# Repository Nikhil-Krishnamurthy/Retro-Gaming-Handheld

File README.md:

# Retro-Gaming-Handheld
This project was creating a gaming handheld from scratch, including cadding the case and designing the pcb. This handheld will run retro games up to the SNES.

Key Features
Esp32 powered emulation   
RGB444 7in screen    
Dedicated sound system    
Cold swappable storage system    
Rechargable 3500mAh battery    
USB C data transfer to computer    
USB C powered charging    

Schematic   

Power   

Buttons   

Screen   

Data   

Sound   

ESP 32   

PCB Layout   

Case

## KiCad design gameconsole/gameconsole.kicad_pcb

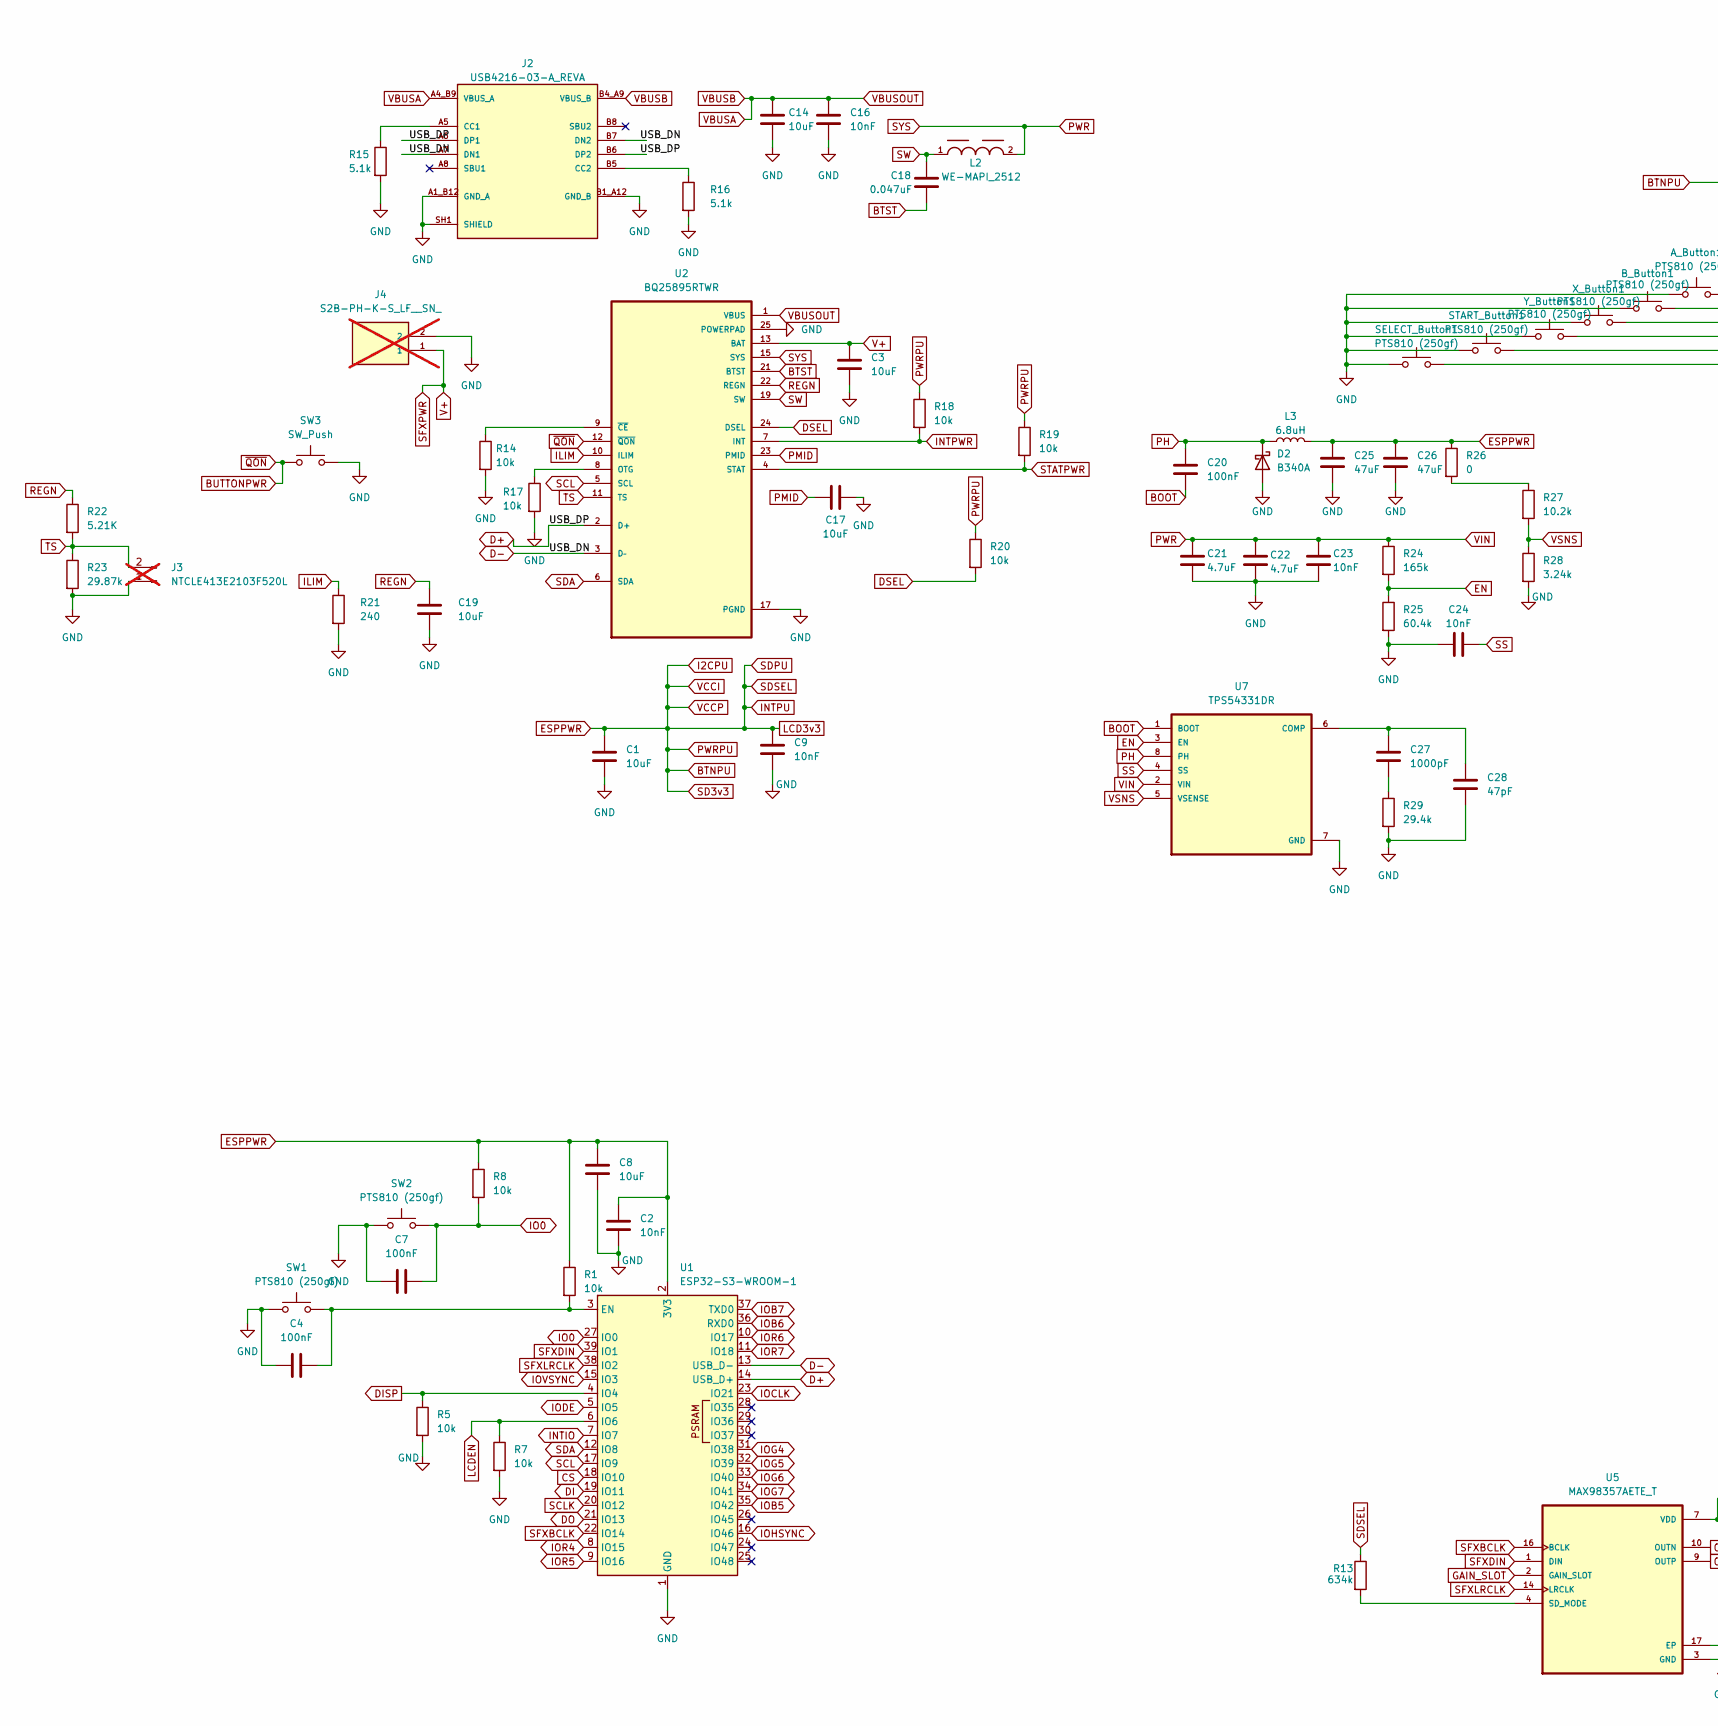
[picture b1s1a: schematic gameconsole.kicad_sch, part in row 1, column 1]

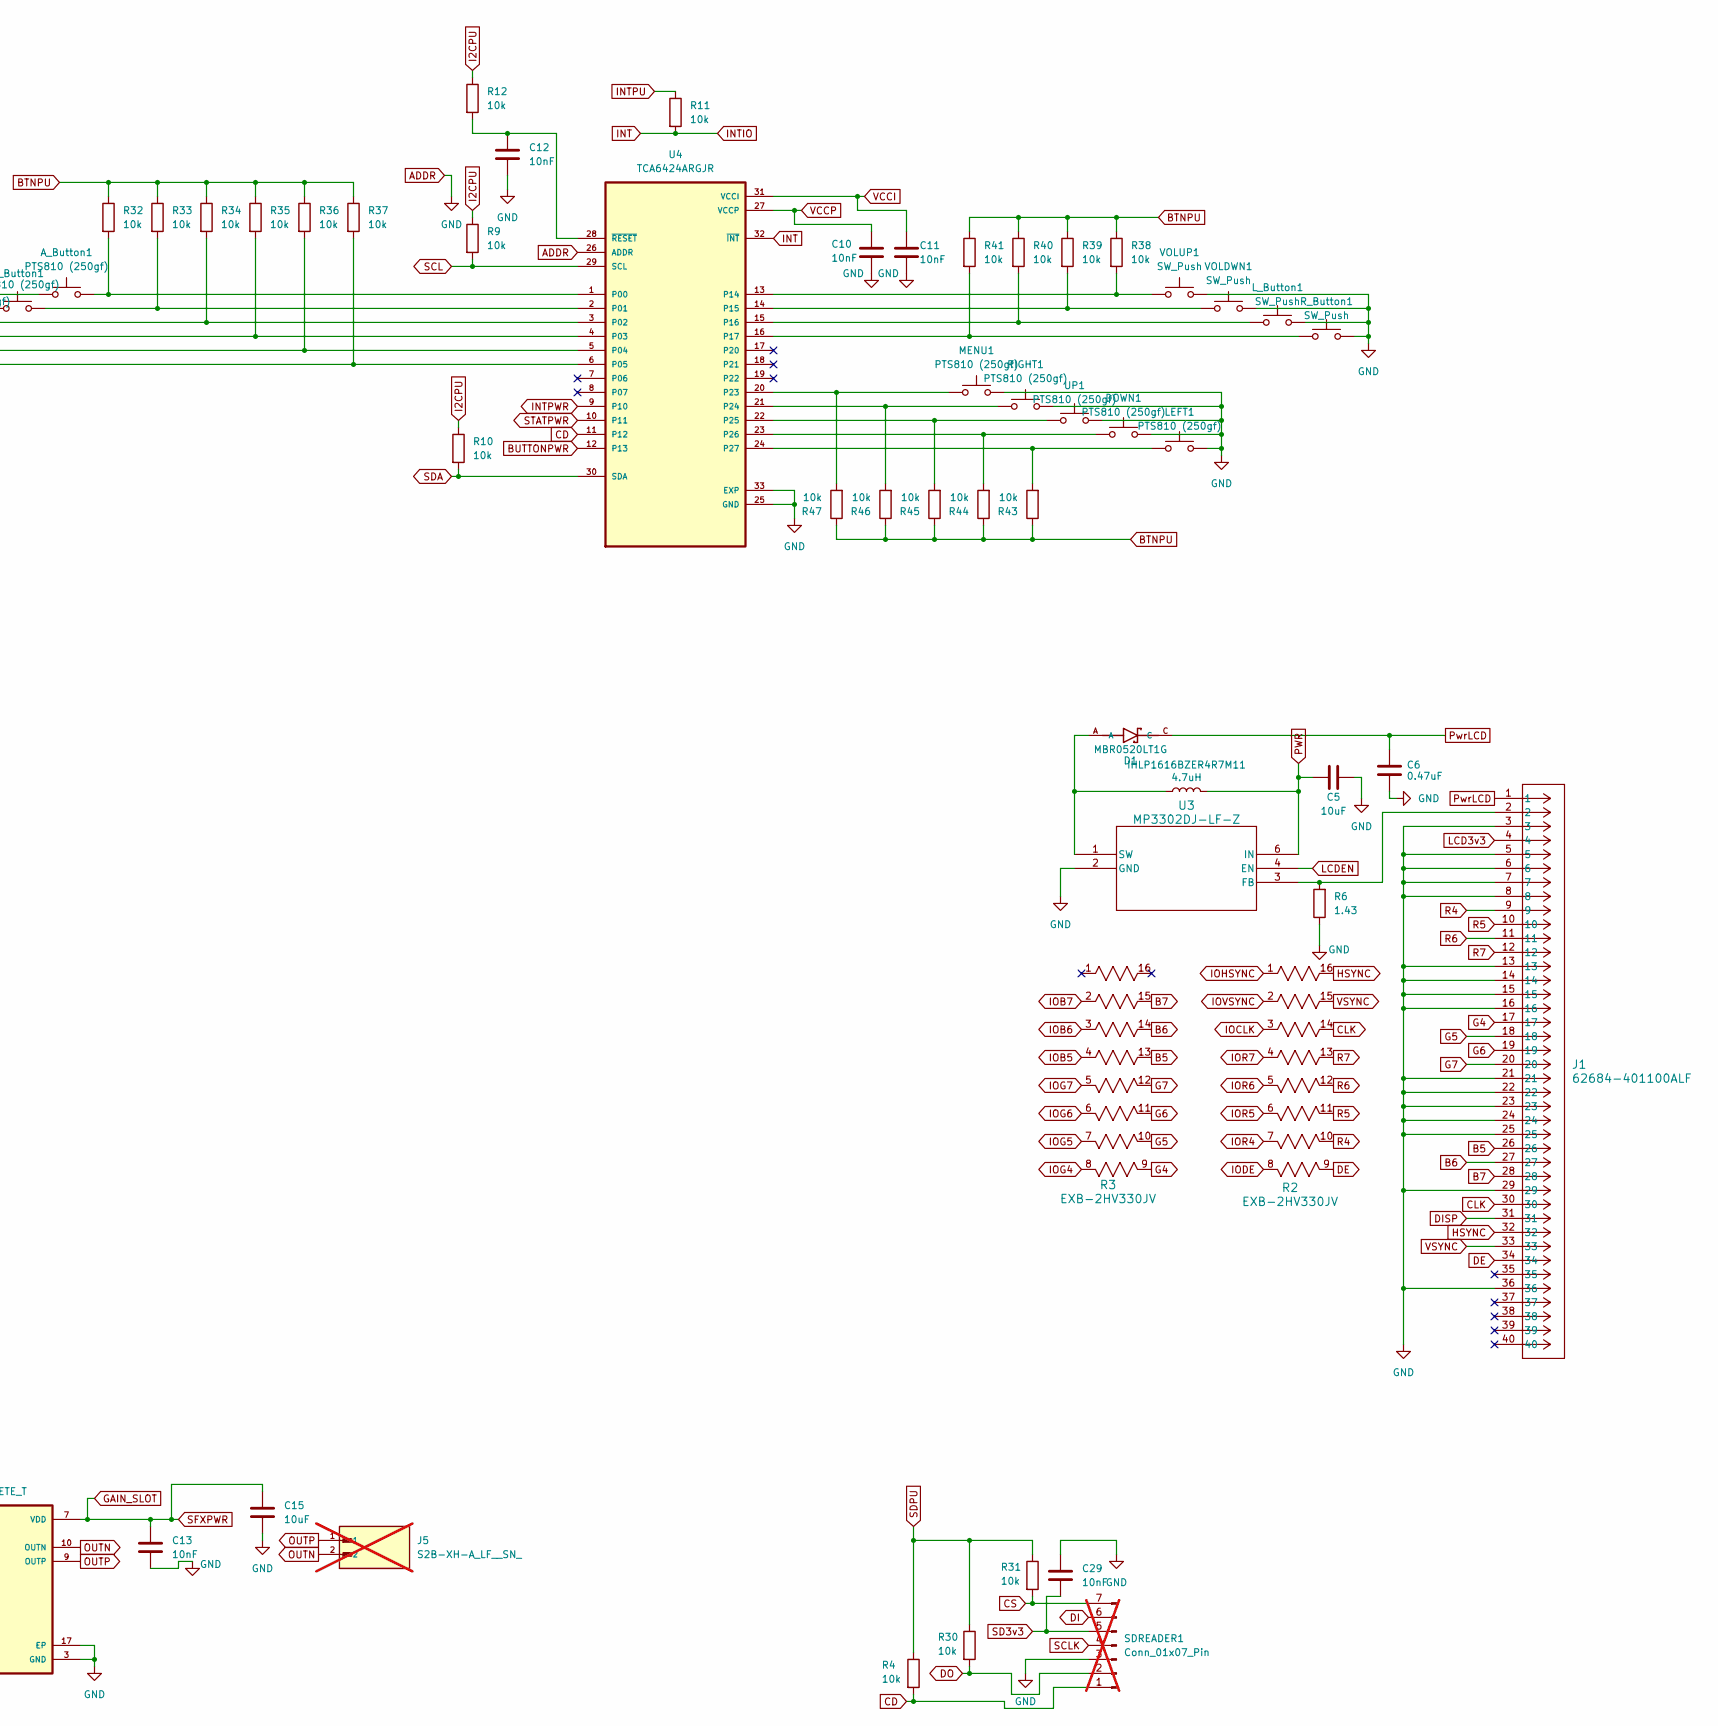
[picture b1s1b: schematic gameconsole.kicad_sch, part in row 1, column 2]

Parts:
A_Button1: PTS810 (250gf); SW_PTS810_SJM_250_SMTR_LFS
B_Button1: PTS810 (250gf); SW_PTS810_SJM_250_SMTR_LFS
C1, C3, C5, C8, C14, C15, C17, C19: 10uF; CAPC3216X180N
C2, C9, C10, C11, C12, C13, C16, C23, C24, C29: 10nF; CAPC1608X90N
C4, C7, C20: 100nF; CAPC1608X90N
C6: 0.47uF; CAPC1608X90N
C18: 0.047uF; C_0805_2012Metric_Pad1.18x1.45mm_HandSolder
C21, C22: 4.7uF; CAPC3216X180N
C25, C26: 47uF; CAPC3216X180N
C27: 1000pF; C_0805_2012Metric_Pad1.18x1.45mm_HandSolder
C28: 47pF; C_0805_2012Metric_Pad1.18x1.45mm_HandSolder
D1: MBR0520LT1G; SOD3716X135N
D2: B340A; DIOM5226X230N
DOWN1: PTS810 (250gf); SW_PTS810_SJM_250_SMTR_LFS
IHLP1616BZER4R7M11: 4.7uH; IND_IHLP-1616BZ_VIS
J1: 62684-401100ALF; CONN_62684-401100ALF_AMP
J2: USB4216-03-A_REVA; GCT_USB4216-03-A_REVA; PARTREV A
J3: NTCLE413E2103F520L; JST_S2B-PH-K-S_LF__SN_; not fitted
J4: S2B-PH-K-S_LF__SN_; JST_S2B-PH-K-S_LF__SN_; not fitted
J5: S2B-XH-A_LF__SN_; JST_S2B-XH-A_LF__SN_; PARTREV 27-1-20; not fitted
L2: WE-MAPI_2512; WE-MAPI_4020
L3: 6.8uH; INDPM7366X300N
LEFT1: PTS810 (250gf); SW_PTS810_SJM_250_SMTR_LFS
L_Button1: SW_Push; SW_TL3330AF130QG
MENU1: PTS810 (250gf); SW_PTS810_SJM_250_SMTR_LFS
R1, R4, R5, R7, R8, R9, R10, R11, R12, R14, R17, R18, R19, R20, R30, R31, R32, R33, R34, R35, R36, R37, R38, R39, R40, R41, R43, R44, R45, R46, R47: 10k; R_0805_2012Metric_Pad1.20x1.40mm_HandSolder
R2, R3: EXB-2HV330JV; RESCAXE50P380X160X55-16N
R6: 1.43; R_0805_2012Metric_Pad1.20x1.40mm_HandSolder
R13: 634k; R_0805_2012Metric_Pad1.20x1.40mm_HandSolder
R15, R16: 5.1k; R_0805_2012Metric_Pad1.20x1.40mm_HandSolder
R21: 240; R_0805_2012Metric_Pad1.20x1.40mm_HandSolder
R22: 5.21K; R_0805_2012Metric_Pad1.20x1.40mm_HandSolder
R23: 29.87k; R_0805_2012Metric_Pad1.20x1.40mm_HandSolder
R24: 165k; R_0805_2012Metric_Pad1.20x1.40mm_HandSolder
R25: 60.4k; R_0805_2012Metric_Pad1.20x1.40mm_HandSolder
R26: 0; R_0805_2012Metric_Pad1.20x1.40mm_HandSolder
R27: 10.2k; R_0805_2012Metric_Pad1.20x1.40mm_HandSolder
R28: 3.24k; R_0805_2012Metric_Pad1.20x1.40mm_HandSolder
R29: 29.4k; R_0805_2012Metric_Pad1.20x1.40mm_HandSolder
RIGHT1: PTS810 (250gf); SW_PTS810_SJM_250_SMTR_LFS
R_Button1: SW_Push; SW_TL3330AF130QG
SDREADER1: Conn_01x07_Pin; PinHeader_1x07_P2.54mm_Vertical; not fitted
SELECT_Button1: PTS810 (250gf); SW_PTS810_SJM_250_SMTR_LFS
START_Button1: PTS810 (250gf); SW_PTS810_SJM_250_SMTR_LFS
SW1, SW2: PTS810 (250gf); SW_PTS810_SJM_250_SMTR_LFS
SW3: SW_Push; SW_TL3330AF130QG
U1: ESP32-S3-WROOM-1
U2: BQ25895RTWR; QFN50P400X400X80-25N
U3: MP3302DJ-LF-Z; TSOT23-5_3x3x1p7_MNP
U4: TCA6424ARGJR; QFN50P500X500X60-33N
U5: MAX98357AETE_T; QFN50P300X300X80-17N
U7: TPS54331DR; SOIC127P599X175-8N
UP1: PTS810 (250gf); SW_PTS810_SJM_250_SMTR_LFS
VOLDWN1: SW_Push; SW_TL3330AF130QG
VOLUP1: SW_Push; SW_TL3330AF130QG
X_Button1: PTS810 (250gf); SW_PTS810_SJM_250_SMTR_LFS
Y_Button1: PTS810 (250gf); SW_PTS810_SJM_250_SMTR_LFS

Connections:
ADDR: A_Button1.1, B_Button1.1, C1.2, C2.2, C3.2, C4.2, C5.2, C6.2, C7.2, C8.2, C9.2, C10.2, C11.2, C12.2, C13.2, C14.2, C15.2, C16.2, C17.2, C19.2, C21.2, C22.2, C23.2, C24.1, C25.2, C26.2, C28.2, C29.1, D2.2 (A), DOWN1.2, J1.3, J1.5, J1.6, J1.7, J1.8, J1.13, J1.14, J1.15, J1.16, J1.21, J1.22, J1.23, J1.24, J1.25, J1.29, J1.36, J2.A1_B12 (GND_A), J2.B1_A12 (GND_B), J2.SH1 (SHIELD), J2.SH2 (SHIELD), J2.SH3 (SHIELD), J2.SH4 (SHIELD), J3.1, J4.2, LEFT1.2, L_Button1.2, MENU1.2, R5.2, R6.1, R7.2, R14.2, R15.2, R16.2, R17.2, R21.2, R23.2, R25.2, R28.2, R29.2, RIGHT1.2, R_Button1.2, SDREADER1.3, SELECT_Button1.1, START_Button1.1, SW1.1, SW2.1, SW3.2, U1.1 (GND), U1.40 (GND), U1.41 (GND), U2.17 (PGND), U2.18 (PGND), U2.25 (POWERPAD), U3.2 (GND), U4.25 (GND), U4.26 (ADDR), U4.33 (EXP), U5.3 (GND), U5.11 (GND), U5.15 (GND), U5.17 (EP), U7.7 (GND), UP1.2, VOLDWN1.2, VOLUP1.2, X_Button1.1, Y_Button1.1
B5: J1.26, R3.13
B6: J1.27, R3.14
B7: J1.28, R3.15
BOOT: C20.2, U7.1 (BOOT)
BTNPU: C1.1, C2.1, C8.1, C9.1, C10.1, C11.1, C25.1, C26.1, C29.2, J1.4, L3.2, R1.1, R4.1, R8.1, R9.1, R10.1, R11.1, R12.1, R13.1, R18.1, R19.1, R20.1, R26.1, R30.1, R31.1, R32.1, R33.1, R34.1, R35.1, R36.1, R37.1, R38.1, R39.1, R40.1, R41.1, R43.1, R44.1, R45.1, R46.1, R47.1, SDREADER1.5, U1.2 (3V3), U4.27 (VCCP), U4.31 (VCCI)
BTST: C18.2, U2.21 (BTST)
BUTTONPWR: SW3.1, U2.12 (~QON), U4.12 (P13)
CD: R4.2, SDREADER1.1, U4.11 (P12)
CLK: J1.30, R2.14
CS: R31.2, SDREADER1.7, U1.18 (IO10)
D+: J2.A6 (DP1), J2.B6 (DP2), U1.14 (USB_D+), U2.2 (D+)
D-: J2.A7 (DN1), J2.B7 (DN2), U1.13 (USB_D-), U2.3 (D–)
DE: J1.34, R2.9
DI: SDREADER1.6, U1.19 (IO11)
DISP: J1.31, R5.1, U1.4 (IO4)
DO: R30.2, SDREADER1.2, U1.21 (IO13)
DSEL: R20.2, U2.24 (DSEL)
EN: R24.2, R25.1, U7.3 (EN)
G4: J1.17, R3.9
G5: J1.18, R3.10
G6: J1.19, R3.11
G7: J1.20, R3.12
GAIN_SLOT: C3.1, C13.1, C15.1, J4.1, U2.13 (BAT), U2.14 (BAT), U5.2 (GAIN_SLOT), U5.7 (VDD), U5.8 (VDD)
HSYNC: J1.32, R2.16
ILIM: R21.1, U2.10 (ILIM)
INT: R11.2, U1.7 (IO7), U4.32 (~INT)
INTPWR: R18.2, U2.7 (INT), U4.9 (P10)
IO0: C7.1, R8.2, SW2.2, U1.27 (IO0)
IOB5: R3.4, U1.35 (IO42)
IOB6: R3.3, U1.36 (RXD0)
IOB7: R3.2, U1.37 (TXD0)
IOCLK: R2.3, U1.23 (IO21)
IODE: R2.8, U1.5 (IO5)
IOG4: R3.8, U1.31 (IO38)
IOG5: R3.7, U1.32 (IO39)
IOG6: R3.6, U1.33 (IO40)
IOG7: R3.5, U1.34 (IO41)
IOHSYNC: R2.1, U1.16 (IO46)
IOR4: R2.7, U1.8 (IO15)
IOR5: R2.6, U1.9 (IO16)
IOR6: R2.5, U1.10 (IO17)
IOR7: R2.4, U1.11 (IO18)
IOVSYNC: R2.2, U1.15 (IO3)
LCDEN: R7.1, U1.6 (IO6), U3.4 (EN)
unnamed: C27.2, R29.1
unnamed: J2.A5 (CC1), R15.1
unnamed: J2.B5 (CC2), R16.1
unnamed: R26.2, R27.1
unnamed: C4.1, R1.2, SW1.2, U1.3 (EN)
unnamed: R17.1, U2.8 (OTG)
unnamed: R14.1, U2.9 (~CE)
unnamed: J1.2, R6.2, U3.3 (FB)
unnamed: D1.A, IHLP1616BZER4R7M11.1, U3.1 (SW)
unnamed: A_Button1.2, R32.2, U4.1 (P00)
unnamed: B_Button1.2, R33.2, U4.2 (P01)
unnamed: R34.2, U4.3 (P02), X_Button1.2
unnamed: R35.2, U4.4 (P03), Y_Button1.2
unnamed: R36.2, START_Button1.2, U4.5 (P04)
unnamed: R37.2, SELECT_Button1.2, U4.6 (P05)
unnamed: R38.2, U4.13 (P14), VOLUP1.1
unnamed: R39.2, U4.14 (P15), VOLDWN1.1
unnamed: L_Button1.1, R40.2, U4.15 (P16)
unnamed: R41.2, R_Button1.1, U4.16 (P17)
unnamed: MENU1.1, R47.2, U4.20 (P23)
unnamed: R46.2, RIGHT1.1, U4.21 (P24)
unnamed: R45.2, U4.22 (P25), UP1.1
unnamed: DOWN1.1, R44.2, U4.23 (P26)
unnamed: LEFT1.1, R43.2, U4.24 (P27)
unnamed: C12.1, R12.2, U4.28 (~RESET)
unnamed: R13.2, U5.4 (SD_MODE)
unnamed: C27.1, C28.1, U7.6 (COMP)
OUTN: J5.2, U5.10 (OUTN)
OUTP: J5.1, U5.9 (OUTP)
PH: C20.1, D2.1 (K), L3.1, U7.8 (PH)
PMID: C17.1, U2.23 (PMID)
PWR: C5.1, C21.1, C22.1, C23.1, IHLP1616BZER4R7M11.2, L2.2, R24.1, U2.15 (SYS), U2.16 (SYS), U3.6 (IN), U7.2 (VIN)
PwrLCD: C6.1, D1.C, J1.1
R4: J1.9, R2.10
R5: J1.10, R2.11
R6: J1.11, R2.12
R7: J1.12, R2.13
REGN: C19.1, R22.1, U2.22 (REGN)
SCL: R9.2, U1.17 (IO9), U2.5 (SCL), U4.29 (SCL)
SCLK: SDREADER1.4, U1.20 (IO12)
SDA: R10.2, U1.12 (IO8), U2.6 (SDA), U4.30 (SDA)
SFXBCLK: U1.22 (IO14), U5.16 (BCLK)
SFXDIN: U1.39 (IO1), U5.1 (DIN)
SFXLRCLK: U1.38 (IO2), U5.14 (LRCLK)
SS: C24.2, U7.4 (SS)
STATPWR: R19.2, U2.4 (STAT), U4.10 (P11)
SW: C18.1, L2.1, U2.19 (SW), U2.20 (SW)
TS: J3.2, R22.2, R23.1, U2.11 (TS)
VBUSA: C14.1, C16.1, J2.A4_B9 (VBUS_A), J2.B4_A9 (VBUS_B), U2.1 (VBUS)
VSNS: R27.2, R28.1, U7.5 (VSENSE)
VSYNC: J1.33, R2.15

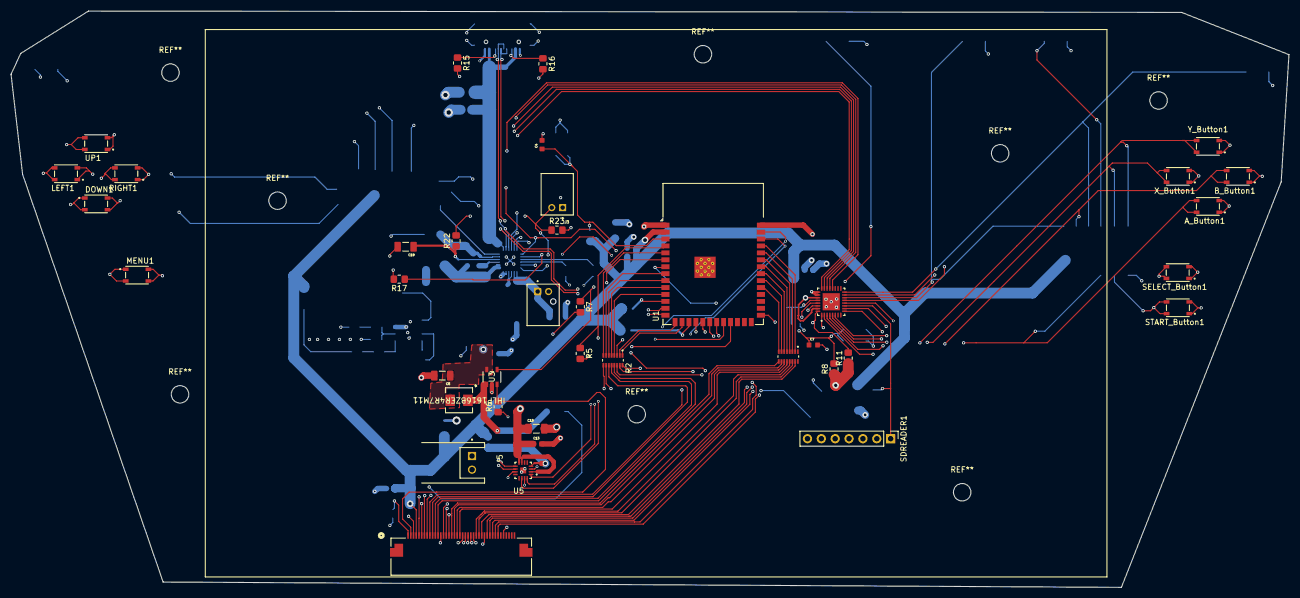
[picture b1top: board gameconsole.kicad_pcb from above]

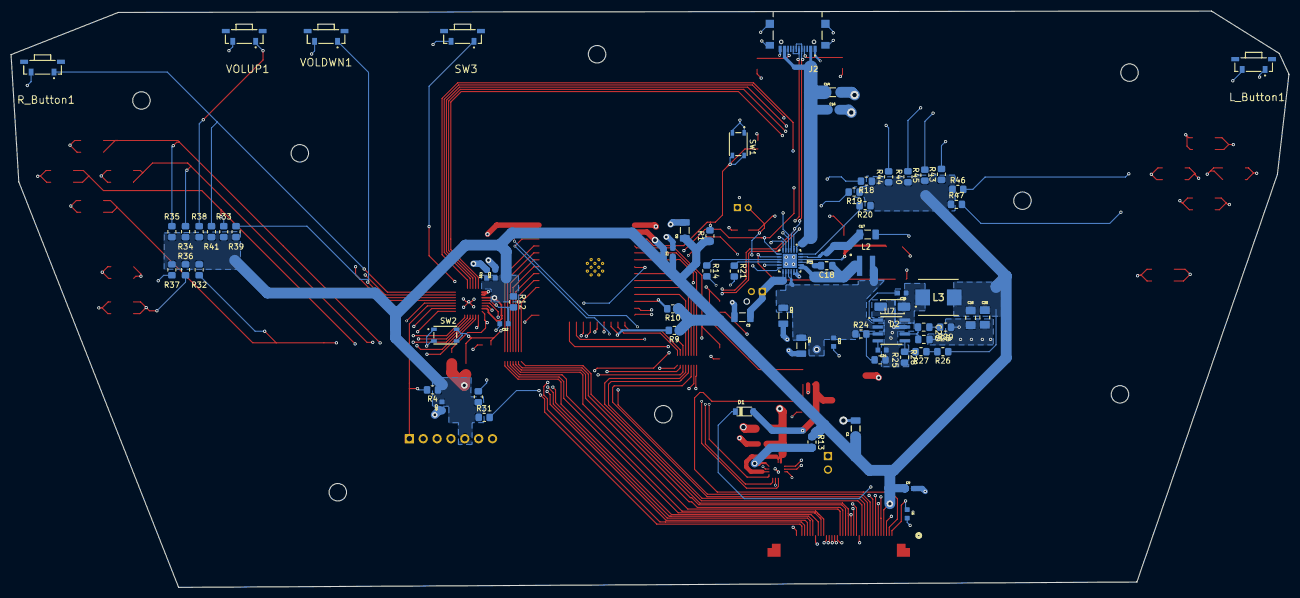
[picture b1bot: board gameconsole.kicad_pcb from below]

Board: 4 copper layers, 234.1 x 105.6 mm, 110 parts (71 on the bottom side), 96 nets.

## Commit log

2026-05-25 PCB files
2026-05-25 Cad Files
2026-05-25 Create test
2026-05-29 Revised Gameconsole kicad schematic
2026-05-29 PCB Drawings
